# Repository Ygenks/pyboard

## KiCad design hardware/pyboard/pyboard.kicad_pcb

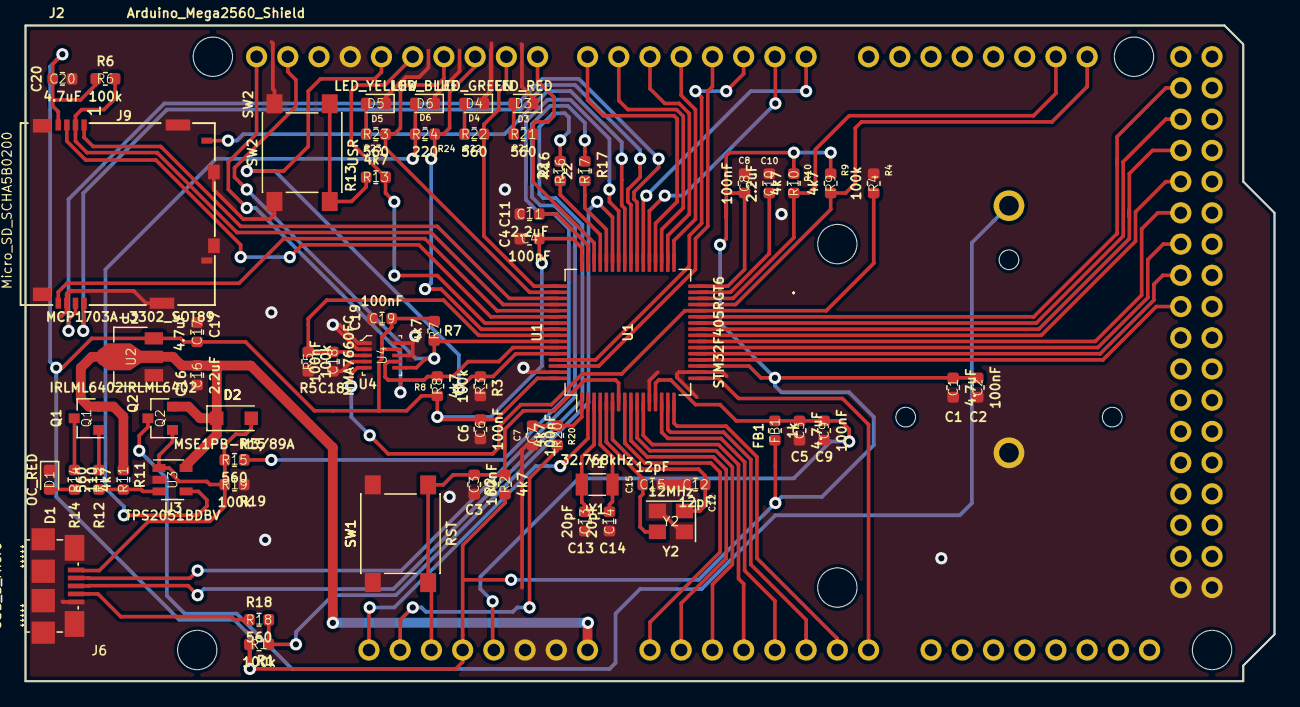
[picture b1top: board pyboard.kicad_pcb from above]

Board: 2 copper layers, 101.6 x 53.3 mm, 65 parts (1 on the bottom side), 75 nets.

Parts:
C1, C5, C17, C20: 4.7uF; C_0603_1608Metric
C2, C3, C4, C6, C7, C8, C9, C18, C19: 100nF; C_0603_1608Metric
C10, C11, C16: 2.2uF; C_0603_1608Metric
C12, C15: 12pF; C_0603_1608Metric
C13, C14: 20pF; C_0603_1608Metric
D1: OC_RED; LED_0603_1608Metric
D2: MSE1PB-M3/89A; D_SOD-123F
D3: LED_RED; LED_0603_1608Metric
D4: LED_GREEN; LED_0603_1608Metric
D5: LED_YELLOW; LED_0603_1608Metric
D6: LED_BLUE; LED_0603_1608Metric
FB1: 1k; R_0603_1608Metric
J1: Battery; CH224-2032LF
J2: Arduino_Mega2560_Shield
J6: USB_B_Micro; USB_Micro-B_10118192-0001LF
J9: Micro_SD_SCHA5B0200; microSD_HC_SCHA5B0200
Q1, Q2: IRLML6402; SOT-23
R1, R3, R4, R5, R6, R19: 100k; R_0603_1608Metric
R2, R7, R8, R9, R10, R11, R13, R20: 4k7; R_0603_1608Metric
R12, R15, R18, R21, R22, R23: 560; R_0603_1608Metric
R14: 110; R_0603_1608Metric
R16, R17: 22; R_0603_1608Metric
R24: 220; R_0603_1608Metric
SW1: RST; SW_Push_1P1T_NO_6x6mm_H9.5mm
SW2: USR; SW_Push_1P1T_NO_6x6mm_H9.5mm
U1: STM32F405RGT6; LQFP-64_10x10mm_P0.5mm
U2: MCP1703A-3302_SOT89; SOT-89-3
U3: TPS2051BDBV; SOT-23-5
U4: MMA7660FC; DFN-10_3x3mm
Y1: 32.768kHz; Crystal_SMD_3215-2Pin_3.2x1.5mm
Y2: 12MHz; Crystal_SMD_3225-4Pin_3.2x2.5mm

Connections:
+3V3: C1.2, C2.2, C4.2, C6.2, C8.2, C17.2, C19.1, C20.1, FB1.1, J2.3V3, J9.4, R1.1, R2.1, R6.1, R7.1, R8.1, R9.1, R10.1, U1.19, U1.32, U1.48, U1.64, U2.3, U4.9
/B: D6.2, R24.1, U3.4
/BLU: J2.D10, R24.2, U1.56
/BOOT0: J2.D13, R3.1, U1.60
/BOOT1-MMA-INT: R4.2, U1.28, U4.5
/D+: R16.2, U1.45
/D-: R17.2, U1.44
/G: D4.2, R22.1
/GRN: J2.D9, R22.2, U1.49
/ID: R1.2, R18.2, U1.43
/MMA_AVDD: C18.1, R5.2, U1.57, U4.3
/N1: C13.1, U1.3, Y1.1
/N2: C14.1, U1.4, Y1.2
/R: D3.2, R21.1
/RED: J2.D8, R21.2, U1.46
/SCL: J2.SDA, R7.2, U1.58, U4.6
/SDA: J2.SCL, R8.2, U1.59, U4.7
/SDIO_CK: J9.5, U1.53
/SDIO_CMD: J9.3, U1.54
/SDIO_D0: J9.7, U1.39
/SDIO_D1: J9.8, U1.40
/SDIO_D2: J9.1, U1.51
/SDIO_D3: J9.2, R6.2, U1.52
/SDIO_SW: J9.10, U1.41
/SW: J2.D12, R13.1, U1.55
/USB_D+: J6.D+, R16.1
/USB_D-: J6.D-, R17.1
/USB_ID: J6.ID, R18.1
/USB_VBUS: D2.2, J6.VBUS, Q2.1, R15.1, R19.1, U3.1
/USR-SW: R13.2, SW2.2
/VBUS: R15.2, U1.42
/VCAP_1: C10.2, U1.31
/VCAP_2: C11.2, U1.47
/VRTC: C7.2, R20.1, U1.1
/X1: J2.A4, U1.14
/X2: J2.A5, U1.15
/X3: J2.A6, U1.16
/X4: J2.A7, U1.17
/X5: J2.D36, U1.20
/X6: J2.D34, U1.21
/X7: J2.D32, U1.22
/X8: J2.D30, U1.23
/X11: J2.D28, U1.24
/X12: J2.D26, U1.25
/X18: J2.X18, U1.2
/X19: J2.A0, U1.8
/X20: J2.A1, U1.9
/X21: J2.A2, U1.10
/X22: J2.A3, U1.11
/Y: D5.2, R23.1
/Y1: J2.D1, U1.37
/Y2: J2.D0, U1.38
/Y3: J2.D2, U1.61
/Y4: J2.D3, U1.62
/Y5: J2.D4, U1.33
/Y6: J2.D5, U1.34
/Y7: J2.D6, U1.35
/Y8: J2.D7, U1.36
/Y9: J2.D21, R9.2, U1.29
/Y10: J2.D20, R10.2, U1.30
/Y11: J2.D24, U1.26
/Y12: J2.D22, U1.27
/YEL: J2.D11, R23.2, U1.50
/~OC: R11.2, R12.2, U3.3
/~RST: C3.2, J2.RST1, R2.2, SW1.2, U1.7
GND: C1.1, C2.1, C3.1, C4.1, C5.1, C6.1, C7.1, C8.1, C9.1, C10.1, C11.1, C12.1, C13.2, C14.2, C15.1, C16.1, C17.1, C18.2, C19.2, C20.2, D1.1, D3.1, D4.1, D5.1, D6.1, J1.2, J2.GND1, J2.GND2, J2.GND3, J2.GND5, J2.GND6, J6.CGND, J6.GND, J9.6, J9.9, J9.11, R3.2, R4.1, R5.1, R19.2, SW1.1, SW2.1, U1.12, U1.18, U1.63, U2.1, U3.2, U4.1, U4.2, U4.4, U4.8, U4.10, Y2.2, Y2.4
unnamed: C12.2, U1.6, Y2.1
unnamed: C15.2, U1.5, Y2.3
unnamed: D1.2, R14.1
unnamed: J1.1, Q2.3
unnamed: J2.IORF, R20.2
unnamed: Q1.1, R12.1
unnamed: Q1.3, R14.2
VCC: C16.2, D2.1, J2.VIN, Q1.2, Q2.2, R11.1, U2.2, U3.5
VDDA: C5.2, C9.2, FB1.2, J2.5V1, U1.13

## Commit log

2019-09-10 Create stm32 symbol
2019-09-15 Update stm symbol
2019-09-17 Create schematic
2019-09-18 Add microsd schematic
2019-09-19 Add ports
2019-09-20 Fix stm symbol
2019-09-23 Fix ferrite bead symbol
2019-09-23 Group symbols by blocks
2019-09-24 Remove prefix from lables
2019-09-24 Annotate schmatics
2019-09-25 Fix ERC errors
2019-10-06 Add footprint for LED
2019-10-08 Add footprints for ICs
2019-10-09 Change power switch model
2019-10-10 WIP: add mosfet and led
2019-10-10 Move overcurrent block
2019-10-11 Add footprint for micro usb
2019-10-11 Add footprint for microSD card
2019-10-13 Add pushbutton footprint
2019-10-14 Add arduino mega footprint
2019-10-14 Add arduino mega schield symbol
2019-10-15 Add footprint for battery cell
2019-10-21 Fix dangling pin
2019-10-25 Generate netlist and place fixed components
2019-10-26 Swap Y and X pins
2019-10-28 Remove ISP pin header
2019-10-29 Place power switch and MOSFETs
2019-10-30 Place voltage regulator
2019-10-31 Place Y2 crystal oscillator
2019-11-05 Place both crystal oscillators
2019-11-09 Change X18 pin binding
2019-11-12 Configure track width
2019-11-15 Route crystal oscillator
2019-11-18 Trace USB
2019-11-19 Trace SDIO #1
2019-11-19 Fix USB terminal resistors
2019-11-20 Add vias for SDIO and leds
2019-11-22 Retrace USB and sd card
2019-11-25 Trace left part of the board
2019-11-28 Trace bottom
2019-11-29 Trace most of the components
2019-12-02 Trace all components
2019-12-03 Add cooper polygon
2019-12-03 Trace all nets
2019-12-09 Fix silk layer
2019-12-24 Add pcb svg
2019-12-29 Add missing datasheets
2020-01-03 Fix wrong via placement
